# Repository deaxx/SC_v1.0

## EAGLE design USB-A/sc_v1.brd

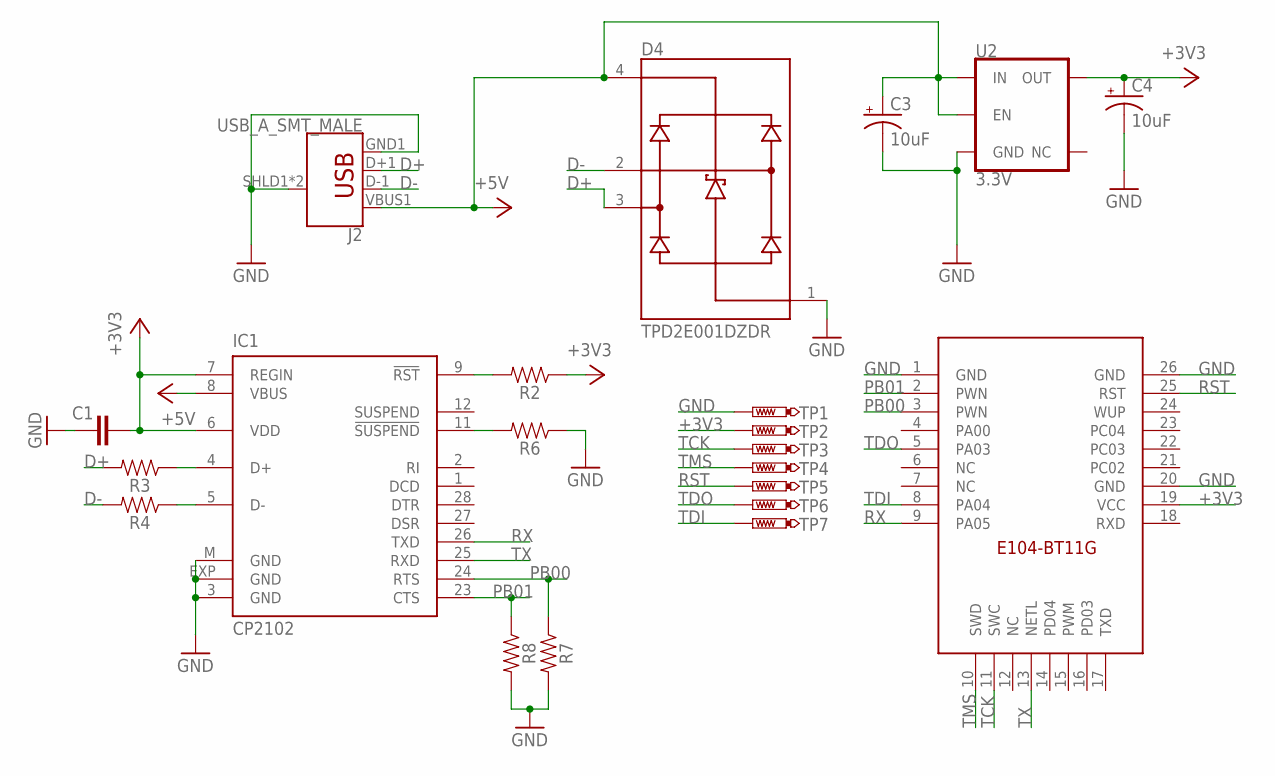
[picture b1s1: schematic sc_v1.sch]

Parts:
C1: 100nf; CAPC1005X40N
C3, C4: 10uF; 0603-POLAR
D4: TPD2E001DZDR; SOT192P237X122-4N
IC1: CP2102; MLP28
J2: USB_A_SMT_MALE; USB-A-SMT-MALE
R2: 4.7k; 0402
R3, R4: 30Ohm; 0402
R6, R7, R8: 10k; 0402
TP1, TP2, TP3, TP4, TP5, TP6, TP7: PTR1TP10R; TP10R
U2: 3.3V; SOT23-5
U$1: E104-BT11G-PCBPCB; E104-BT11G-PCB

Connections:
+3V3: C1.2, C4.+, IC1.6 (VDD), IC1.7 (REGIN), R2.1, TP2.TP, U2.5 (OUT), U$1.19 (VCC)
+5V: C3.+, D4.4 (VCC), IC1.8 (VBUS), J2.VBUS1 (VBUS), U2.1 (IN), U2.3 (EN)
D+: D4.3 (IO2), J2.D+1 (D+), R3.2
D-: D4.2 (IO1), J2.D-1 (D-), R4.2
GND: C1.1, C3.-, C4.-, D4.1 (GND), IC1.3 (GND), IC1.EXP (GND), IC1.M (GND), J2.GND1 (GND), J2.SHLD1 (SHIELD), J2.SHLD2 (SHIELD), R6.1, R7.2, R8.2, TP1.TP, U2.2 (GND), U$1.1 (GND), U$1.20 (GND), U$1.26 (GND)
unnamed: IC1.4 (D+), R3.1
unnamed: IC1.5 (D-), R4.1
unnamed: IC1.9 (!RST), R2.2
unnamed: IC1.11 (!SUSPEND), R6.2
PB00: IC1.24 (RTS), R7.1, U$1.3 (PWN)
PB01: IC1.23 (CTS), R8.1, U$1.2 (PWN)
RST: TP5.TP, U$1.25 (RST)
RX: IC1.26 (TXD), U$1.9 (PA05)
TCK: TP3.TP, U$1.11 (SWC)
TDI: TP7.TP, U$1.8 (PA04)
TDO: TP6.TP, U$1.5 (PA03)
TMS: TP4.TP, U$1.10 (SWD)
TX: IC1.25 (RXD), U$1.13 (NETL)

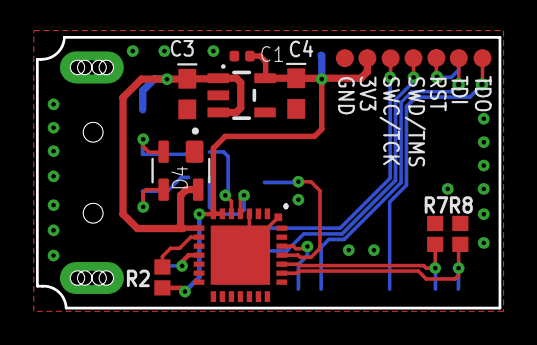
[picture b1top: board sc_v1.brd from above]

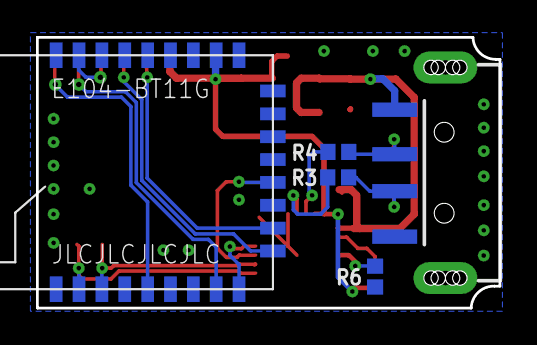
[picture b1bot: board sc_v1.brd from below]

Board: 2 copper layers, 25.7 x 15.0 mm, 21 parts (5 on the bottom side), 18 nets.

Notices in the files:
parts and their libraries:
SparkFun-Resistors: Licensing: Creative Commons ShareAlike 4.0 International - https://creativecommons.org/licenses/by-sa/4.0
